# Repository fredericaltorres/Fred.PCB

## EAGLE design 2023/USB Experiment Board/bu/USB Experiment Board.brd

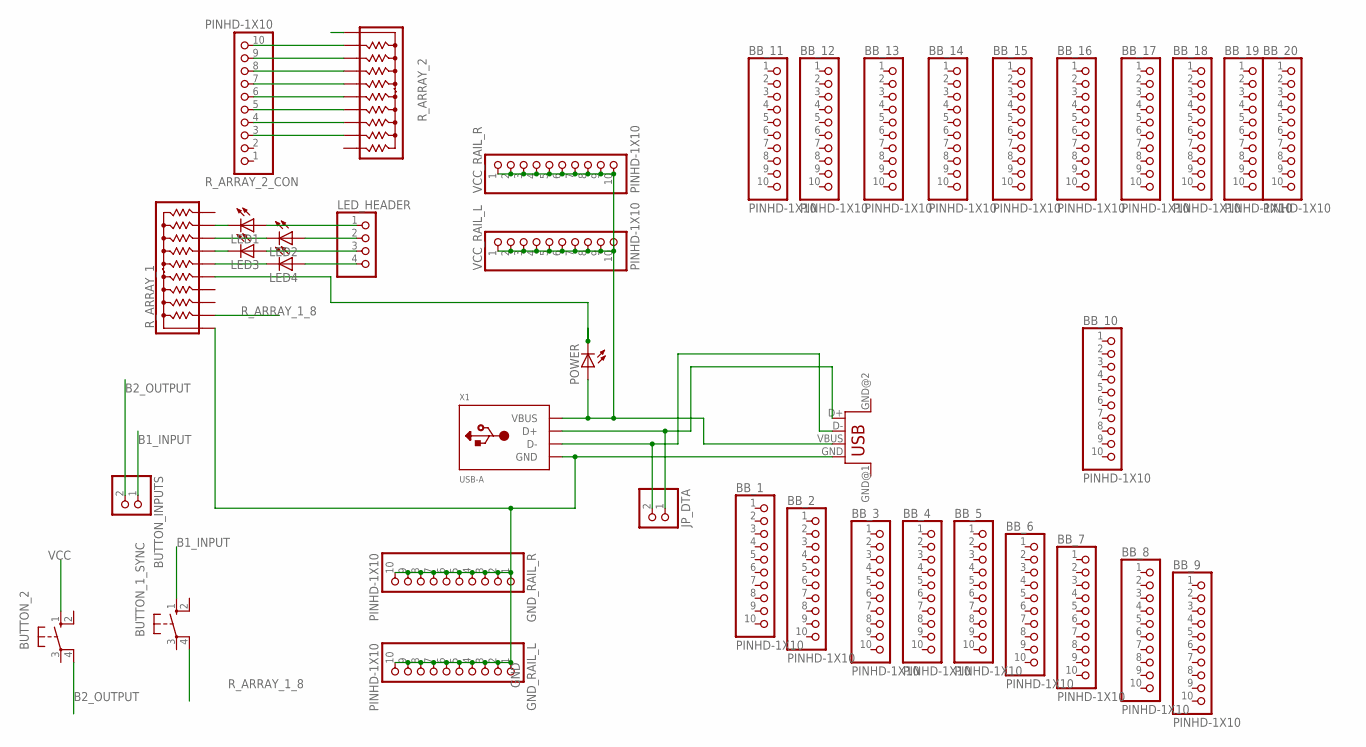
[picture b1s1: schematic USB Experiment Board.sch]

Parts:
BB_1, BB_2, BB_3, BB_4, BB_5, BB_6, BB_7, BB_8, BB_9, BB_10, BB_11, BB_12, BB_13, BB_14, BB_15, BB_16, BB_17, BB_18, BB_19, BB_20: PINHD-1X10; 1X10-BIG
BUTTON_1_SYNC, BUTTON_2: 10-XX; B3F-10XX
BUTTON_INPUTS: PINHD-1X2; 1X02
GND_RAIL_L: PINHD-1X10; 1X10-BIG
GND_RAIL_R: PINHD-1X10; 1X10-BIG
JP_DTA: PINHD-1X2; 1X02
LED1, LED2, LED3, LED4: LEDSMT1206; 1206
LED_HEADER: PINHD-1X4; 1X04
POWER: LEDSMT1206; 1206
R_ARRAY_1, R_ARRAY_2: 4610X; SIP10
R_ARRAY_2_CON: PINHD-1X10; 1X10-BIG
U$1: USB; USB-FEMALE-A-PTH
VCC_RAIL_L: PINHD-1X10; 1X10-BIG
VCC_RAIL_R: PINHD-1X10; 1X10-BIG
X1: USB-A; MOLEX_480371000

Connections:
B1_INPUT: BUTTON_1_SYNC.1 (S), BUTTON_INPUTS.1
B2_OUTPUT: BUTTON_2.4 (P1), BUTTON_INPUTS.2
GND: GND_RAIL_L.1, GND_RAIL_L.2, GND_RAIL_L.3, GND_RAIL_L.4, GND_RAIL_L.5, GND_RAIL_L.6, GND_RAIL_L.7, GND_RAIL_L.8, GND_RAIL_L.9, GND_RAIL_L.10, GND_RAIL_R.1, GND_RAIL_R.2, GND_RAIL_R.3, GND_RAIL_R.4, GND_RAIL_R.5, GND_RAIL_R.6, GND_RAIL_R.7, GND_RAIL_R.8, GND_RAIL_R.9, GND_RAIL_R.10, R_ARRAY_1.1, R_ARRAY_2.1, U$1.GND, X1.4 (GND)
unnamed: R_ARRAY_2.2, R_ARRAY_2_CON.10
unnamed: LED1.C, R_ARRAY_1.9
unnamed: JP_DTA.1, U$1.D+, X1.3 (D+)
unnamed: JP_DTA.2, U$1.D-, X1.2 (D-)
unnamed: LED2.C, R_ARRAY_1.8
unnamed: LED3.C, R_ARRAY_1.7
unnamed: LED4.C, R_ARRAY_1.6
unnamed: LED1.A, LED_HEADER.1
unnamed: LED2.A, LED_HEADER.2
unnamed: LED3.A, LED_HEADER.3
unnamed: LED4.A, LED_HEADER.4
unnamed: R_ARRAY_2.3, R_ARRAY_2_CON.9
unnamed: POWER.C, R_ARRAY_1.5
unnamed: R_ARRAY_2.4, R_ARRAY_2_CON.8
unnamed: R_ARRAY_2.5, R_ARRAY_2_CON.7
unnamed: R_ARRAY_2.6, R_ARRAY_2_CON.6
unnamed: R_ARRAY_2.7, R_ARRAY_2_CON.5
unnamed: R_ARRAY_2.8, R_ARRAY_2_CON.4
unnamed: R_ARRAY_2.9, R_ARRAY_2_CON.3
R_ARRAY_1_8: BUTTON_1_SYNC.4 (P1), R_ARRAY_1.2
VCC: BUTTON_2.1 (S), POWER.A, U$1.VBUS, VCC_RAIL_L.1, VCC_RAIL_L.2, VCC_RAIL_L.3, VCC_RAIL_L.4, VCC_RAIL_L.5, VCC_RAIL_L.6, VCC_RAIL_L.7, VCC_RAIL_L.8, VCC_RAIL_L.9, VCC_RAIL_L.10, VCC_RAIL_R.1, VCC_RAIL_R.2, VCC_RAIL_R.3, VCC_RAIL_R.4, VCC_RAIL_R.5, VCC_RAIL_R.6, VCC_RAIL_R.7, VCC_RAIL_R.8, VCC_RAIL_R.9, VCC_RAIL_R.10, X1.1 (VBUS)

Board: 2 copper layers, 39 parts (0 on the bottom side), 24 nets, no tracks yet.

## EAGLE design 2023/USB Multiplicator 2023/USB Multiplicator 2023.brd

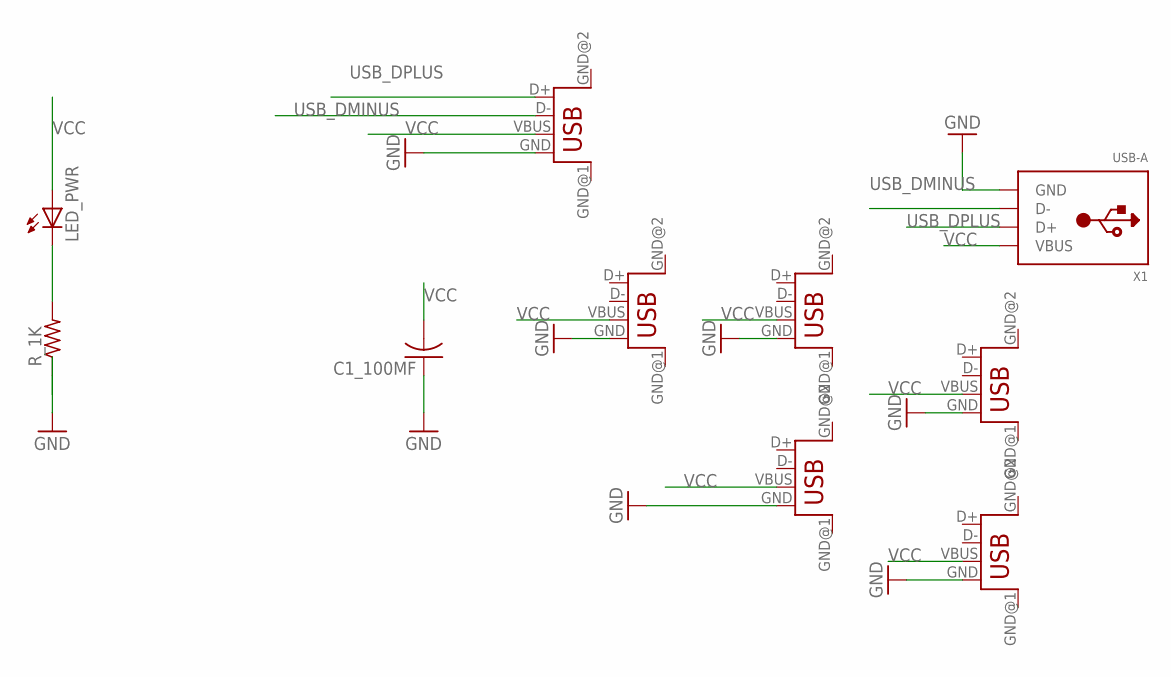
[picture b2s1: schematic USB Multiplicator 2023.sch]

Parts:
C1_100MF: C-US025-030X050; C025-030X050
LED_PWR: LEDSMT1206; 1206
R_1K: R-US_R1206; R1206
USB_OUT_2, USB_OUT_3, USB_OUT_4, USB_OUT_5, USB_OUT_6: USB; USB-FEMALE-A-PTH
USB_OUT_WITH_DATA_1: USB; USB-FEMALE-A-PTH
X1: USB-A; MOLEX_480371000

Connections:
GND: C1_100MF.1, R_1K.1, USB_OUT_2.GND, USB_OUT_3.GND, USB_OUT_4.GND, USB_OUT_5.GND, USB_OUT_6.GND, USB_OUT_WITH_DATA_1.GND, X1.4 (GND)
unnamed: LED_PWR.C, R_1K.2
USB_DMINUS: USB_OUT_WITH_DATA_1.D-, X1.2 (D-)
USB_DPLUS: USB_OUT_WITH_DATA_1.D+, X1.3 (D+)
VCC: C1_100MF.2, LED_PWR.A, USB_OUT_2.VBUS, USB_OUT_3.VBUS, USB_OUT_4.VBUS, USB_OUT_5.VBUS, USB_OUT_6.VBUS, USB_OUT_WITH_DATA_1.VBUS, X1.1 (VBUS)

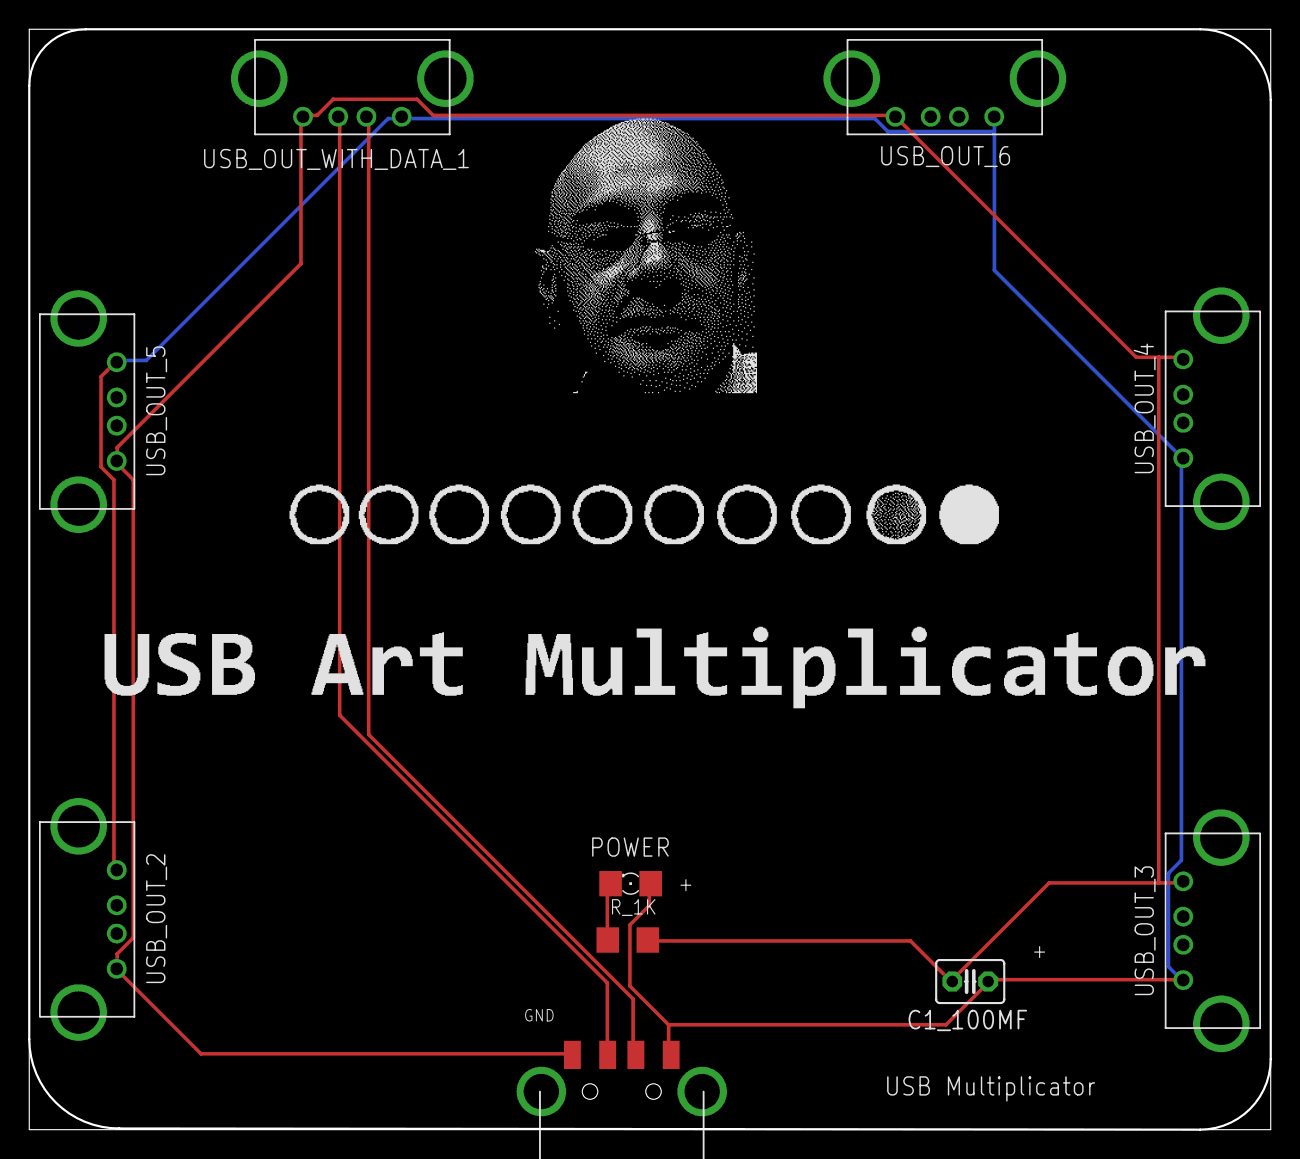
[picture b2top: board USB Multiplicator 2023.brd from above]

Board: 2 copper layers, 88.0 x 78.0 mm, 10 parts (0 on the bottom side), 5 nets.

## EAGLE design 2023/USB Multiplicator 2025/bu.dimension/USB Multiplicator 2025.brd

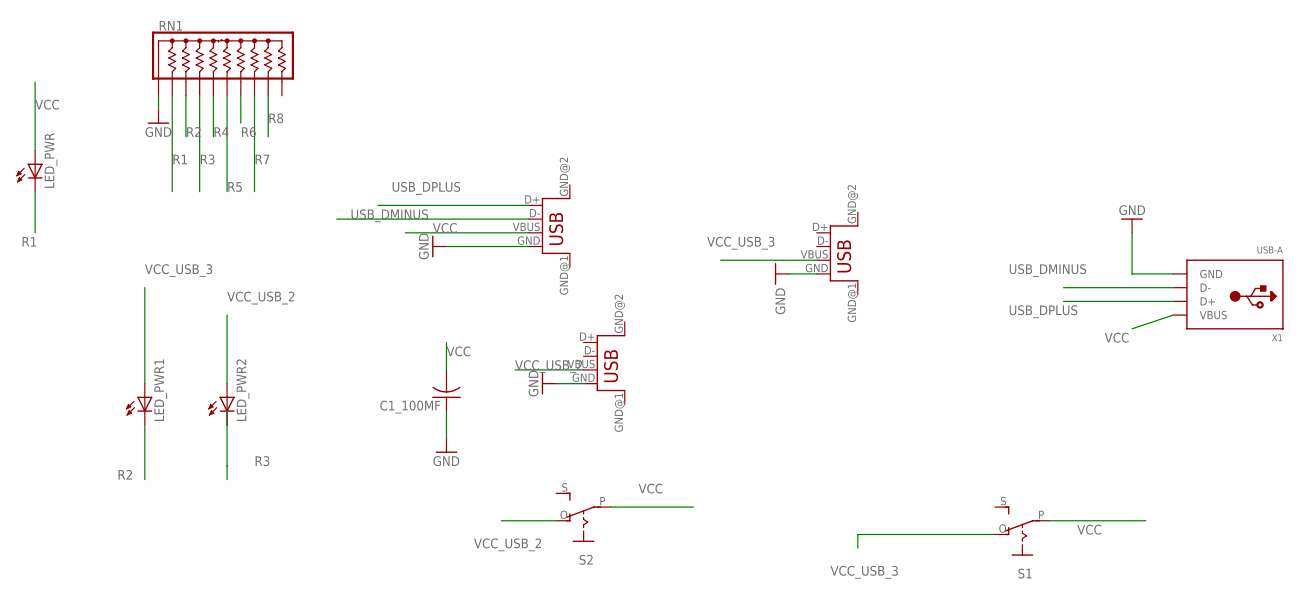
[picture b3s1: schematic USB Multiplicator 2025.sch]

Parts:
C1_100MF: C-US025-030X050; C025-030X050
LED_PWR, LED_PWR1, LED_PWR2: LEDSMT1206; 1206
RN1: 4610X; SIP10
S1, S2: EG1218S; EG1218
USB_OUT_1, USB_OUT_2: USB; USB-FEMALE-A-PTH
USB_OUT_WITH_DATA_1: USB; USB-FEMALE-A-PTH
X1: USB-A; MOLEX_480371000

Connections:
GND: C1_100MF.1, RN1.1, USB_OUT_1.GND, USB_OUT_2.GND, USB_OUT_WITH_DATA_1.GND, X1.4 (GND)
unnamed: USB_OUT_WITH_DATA_1.D-, X1.2 (D-)
unnamed: USB_OUT_WITH_DATA_1.D+, X1.3 (D+)
R1: LED_PWR.C, RN1.2
R2: LED_PWR1.C, RN1.3
R3: LED_PWR2.C, RN1.4
R4: RN1.5
R5: RN1.6
R6: RN1.7
R7: RN1.8
R8: RN1.9
VCC: C1_100MF.2, LED_PWR.A, S1.P, S2.P, USB_OUT_WITH_DATA_1.VBUS, X1.1 (VBUS)
VCC_USB_2: LED_PWR2.A, S2.O, USB_OUT_2.VBUS
VCC_USB_3: LED_PWR1.A, S1.O, USB_OUT_1.VBUS

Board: 2 copper layers, 11 parts (0 on the bottom side), 9 nets, no tracks yet.

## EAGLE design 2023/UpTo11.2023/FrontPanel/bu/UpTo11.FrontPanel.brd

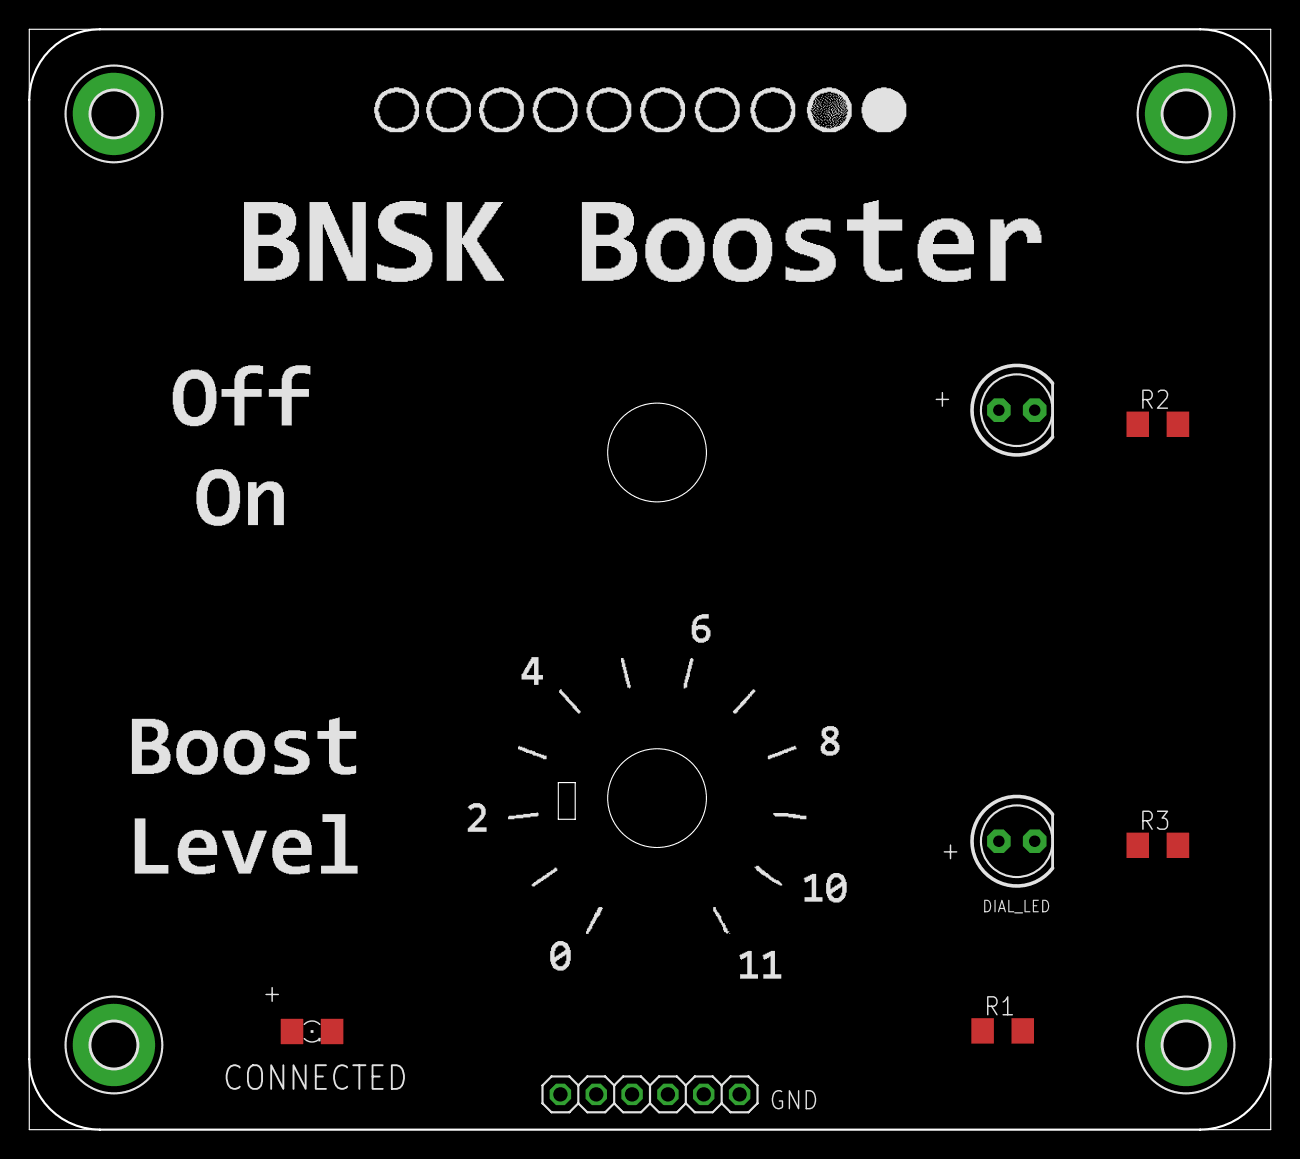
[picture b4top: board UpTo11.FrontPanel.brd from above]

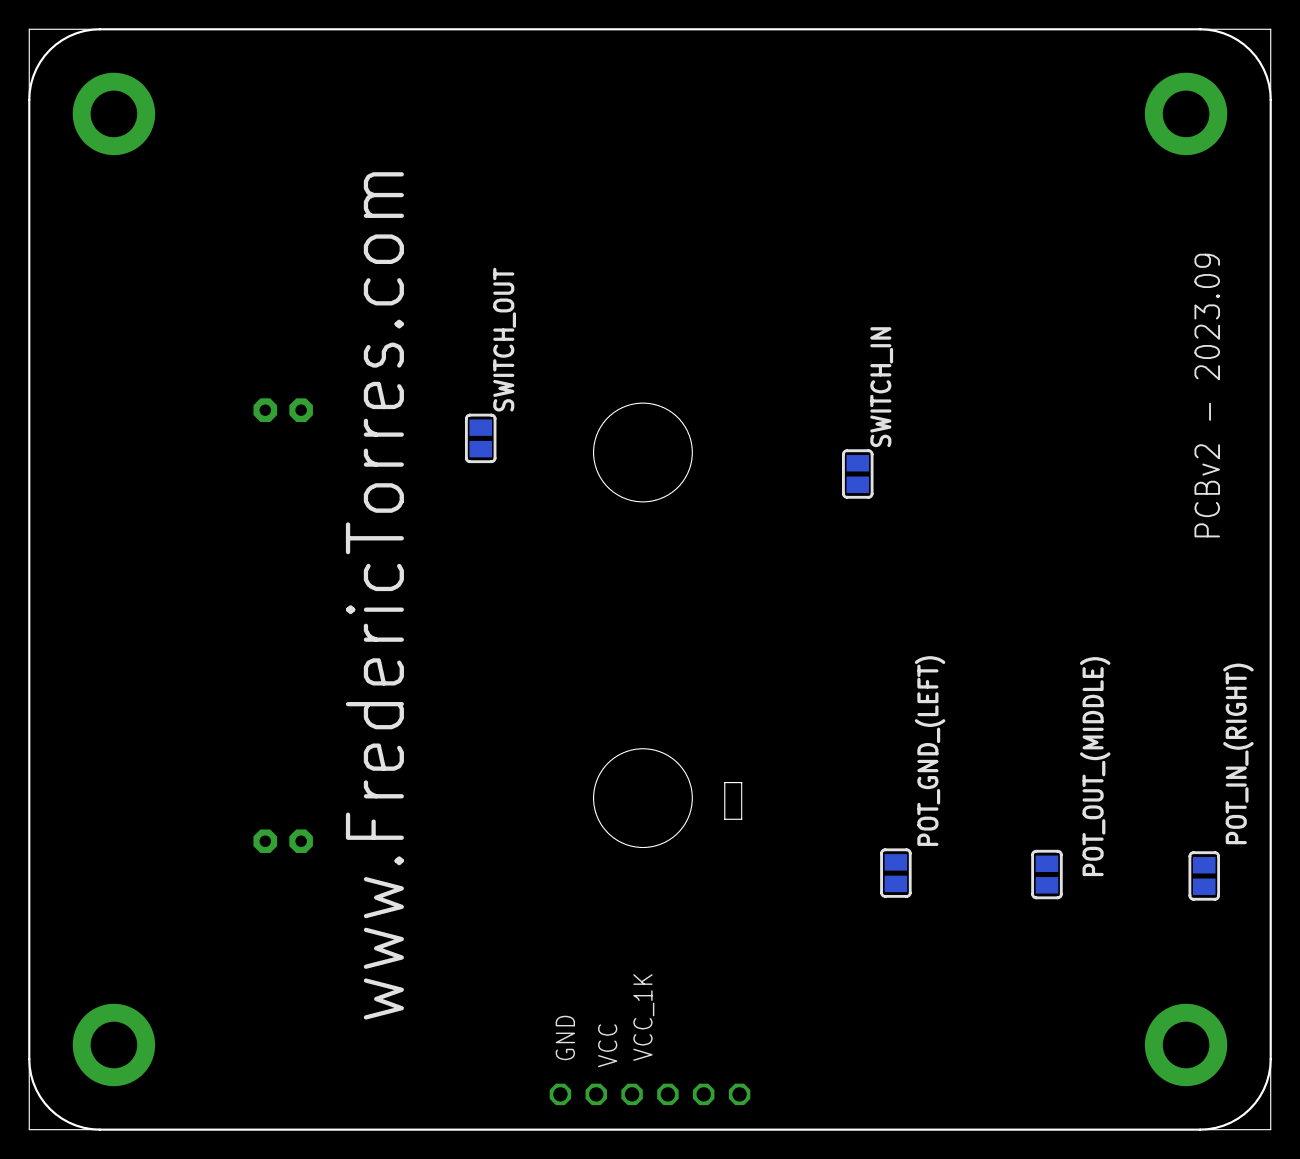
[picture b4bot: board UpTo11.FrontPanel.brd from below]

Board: 2 copper layers, 88.0 x 78.0 mm, 16 parts (5 on the bottom side), 7 nets, no tracks yet.

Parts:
BOOSTER_ON_LED: LED5MM
CONNECTED: 1206
DIAL_LED: LED5MM
FRONT_PANEL_INTERFACE: 1X06
H1, H2, H3, H4: MOUNT-PAD-ROUND3.3; 3,3-PAD
POT_GND_(LEFT): SOLDERJUMPER_REFLOW
POT_IN_(RIGHT): SOLDERJUMPER_REFLOW
POT_OUT_(MIDDLE): SOLDERJUMPER_REFLOW
R1, R2, R3: R1206
SWITCH_IN: SOLDERJUMPER_REFLOW
SWITCH_OUT: SOLDERJUMPER_REFLOW

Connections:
BOOSTER_ON: BOOSTER_ON_LED.A, POT_IN_(RIGHT).2, SWITCH_OUT.2
DIAL_INPUT: DIAL_LED.A, POT_OUT_(MIDDLE).2
GND_EX: FRONT_PANEL_INTERFACE.1, POT_GND_(LEFT).2, R1.1, R2.1, R3.1
unnamed: CONNECTED.C, R1.2
unnamed: BOOSTER_ON_LED.K, R2.2
unnamed: DIAL_LED.K, R3.2
VCC: CONNECTED.A, FRONT_PANEL_INTERFACE.6, SWITCH_IN.2

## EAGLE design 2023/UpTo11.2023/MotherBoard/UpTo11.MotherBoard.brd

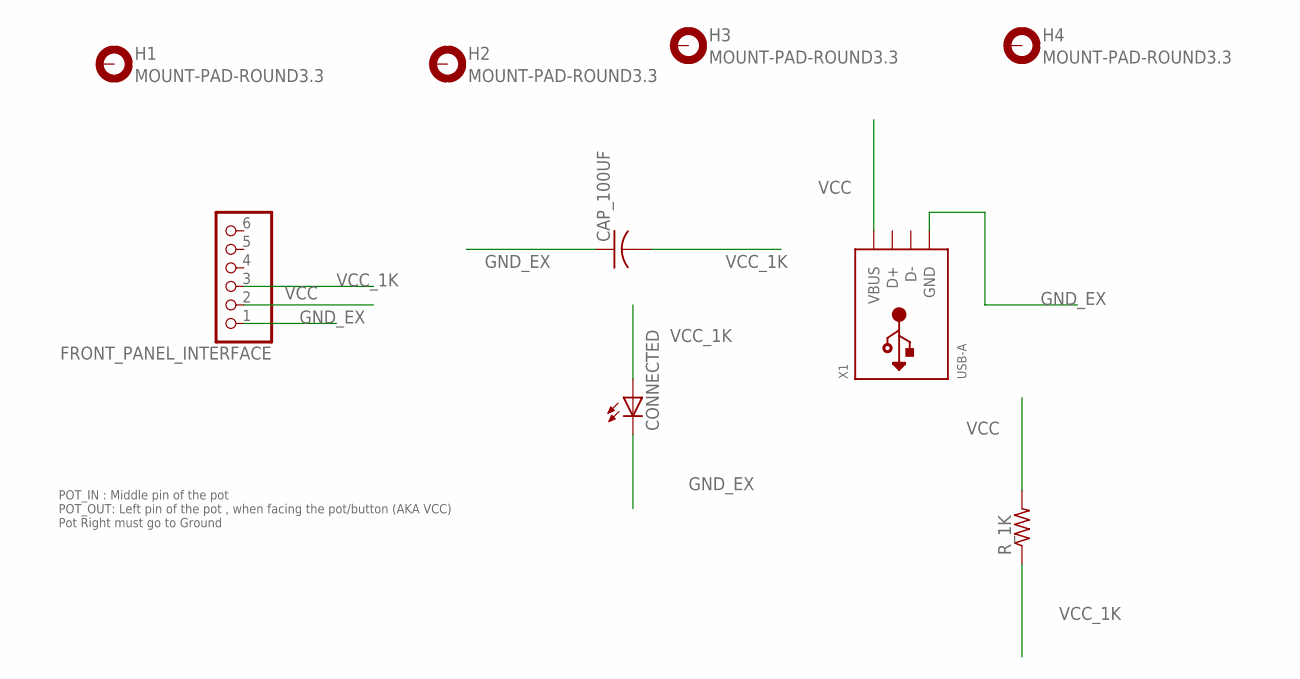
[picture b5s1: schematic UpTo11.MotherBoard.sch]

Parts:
CAP_100UF: C-US025-030X050; C025-030X050
CONNECTED: LEDSMT1206; 1206
FRONT_PANEL_INTERFACE: PINHD-1X6; 1X06
H1, H2, H3, H4: MOUNT-PAD-ROUND3.3; 3,3-PAD
R_1K: R-US_R1206; R1206
X1: USB-A; MOLEX_480371000

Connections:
GND_EX: CAP_100UF.1, CONNECTED.C, FRONT_PANEL_INTERFACE.1, X1.4 (GND)
VCC: FRONT_PANEL_INTERFACE.2, R_1K.2, X1.1 (VBUS)
VCC_1K: CAP_100UF.2, CONNECTED.A, FRONT_PANEL_INTERFACE.3, R_1K.1

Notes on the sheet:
POT_IN : Middle pin of the pot POT_OUT: Left pin of the pot , when facing the pot/button (AKA VCC) Pot Right must go to Ground

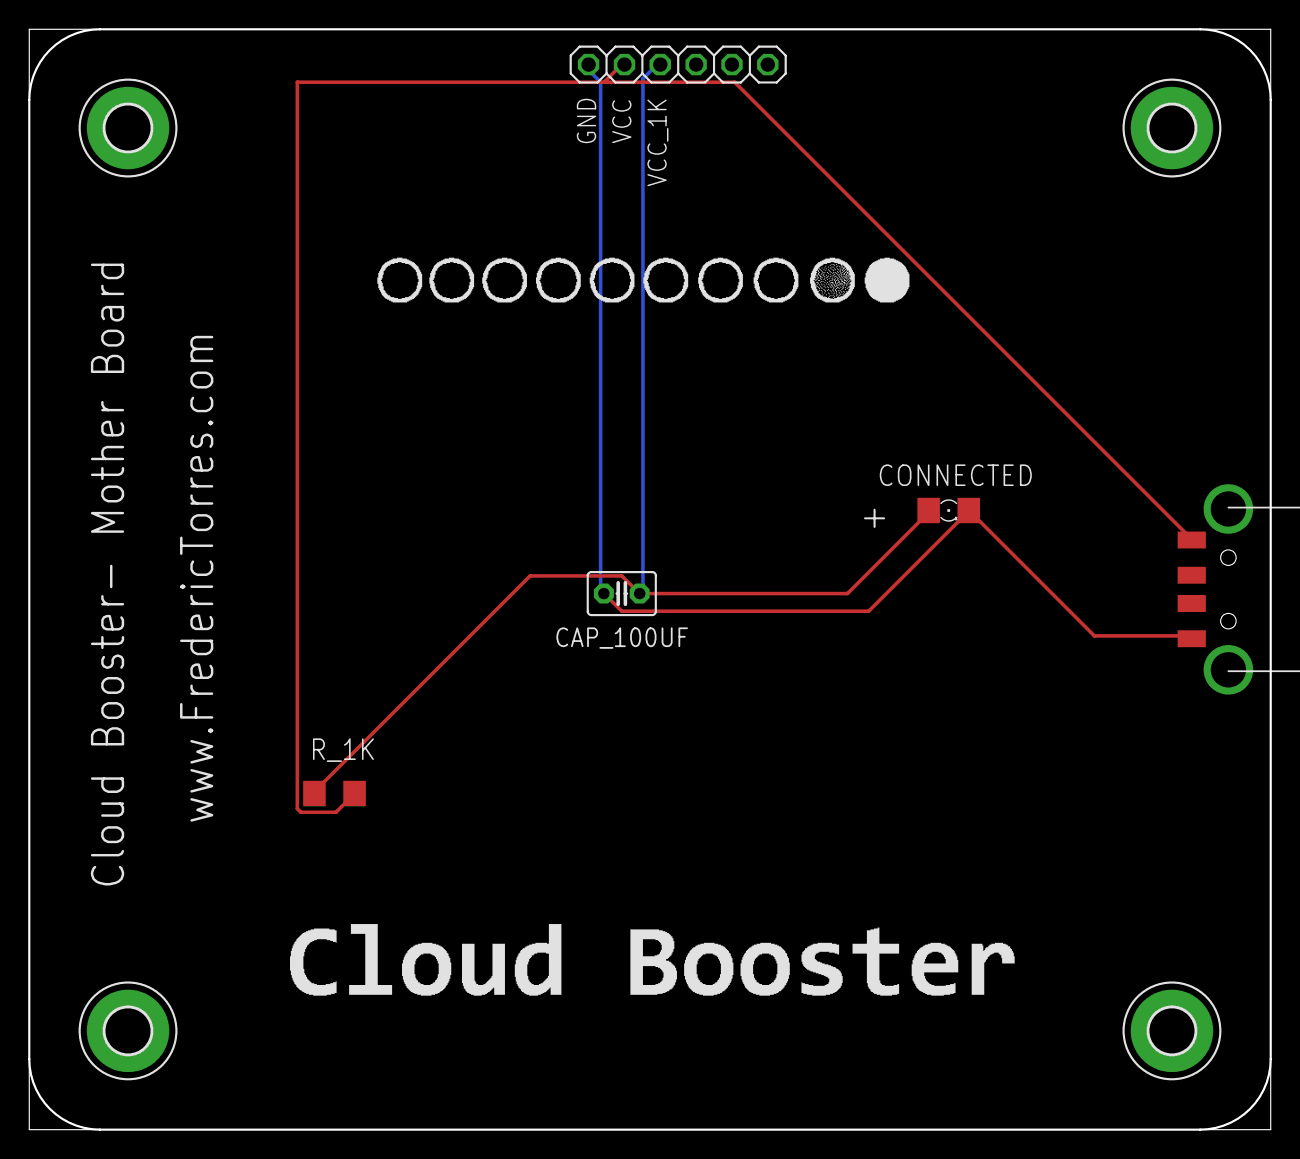
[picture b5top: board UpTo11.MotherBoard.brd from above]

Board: 2 copper layers, 88.0 x 78.0 mm, 9 parts (0 on the bottom side), 3 nets.

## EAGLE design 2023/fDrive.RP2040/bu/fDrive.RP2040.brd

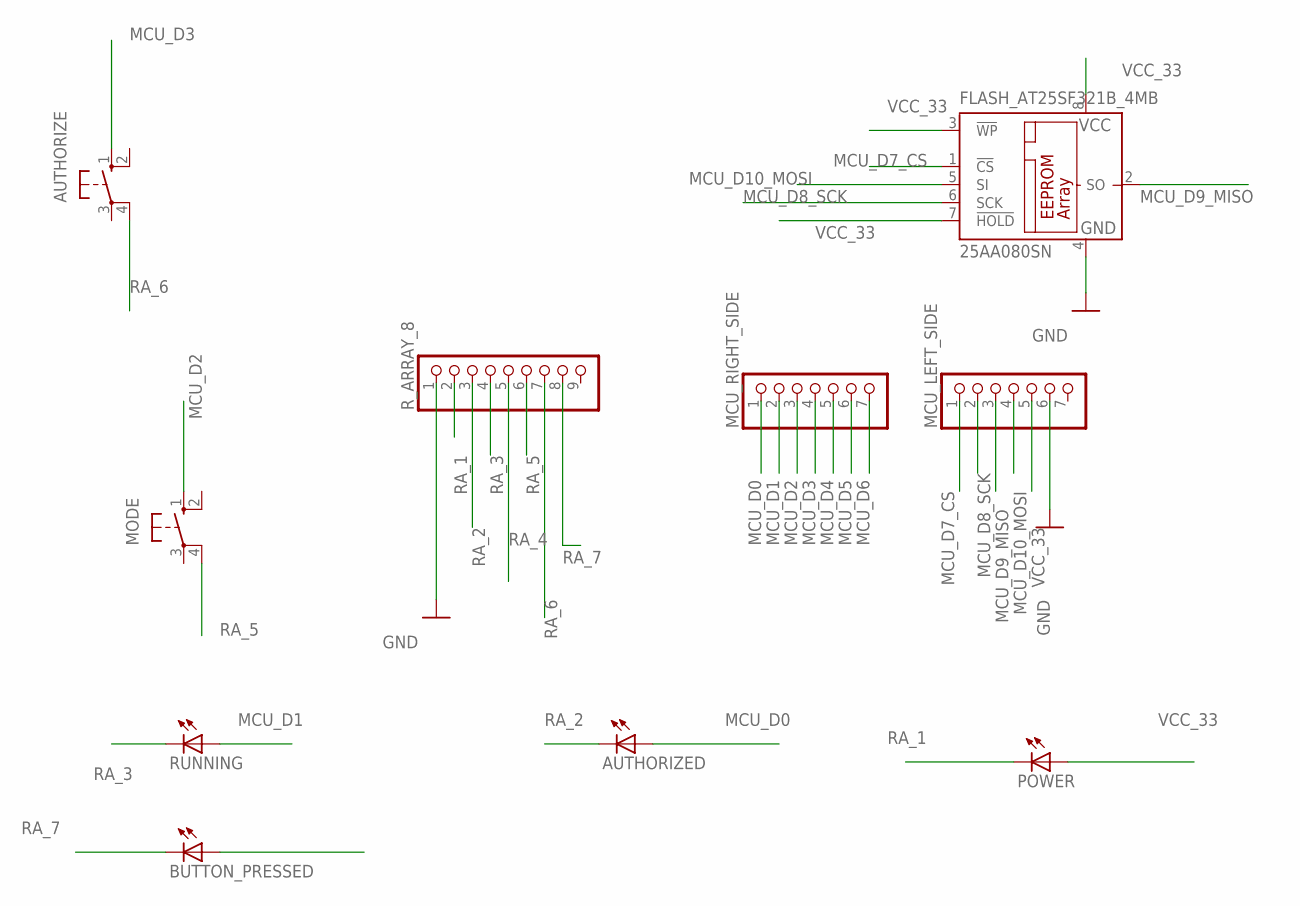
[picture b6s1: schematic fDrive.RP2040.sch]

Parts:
AUTHORIZE: 10-XX; B3F-10XX
AUTHORIZED: LEDSMT1206; 1206
BUTTON_PRESSED: LEDSMT1206; 1206
FLASH_AT25SF321B_4MB: 25AA080SN; SO-08
MCU_LEFT_SIDE: PINHD-1X7; 1X07
MCU_RIGHT_SIDE: PINHD-1X7; 1X07
MODE: 10-XX; B3F-10XX
POWER: LEDSMT1206; 1206
RUNNING: LEDSMT1206; 1206
R_ARRAY_8: PINHD-1X9; 1X09-BIG

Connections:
GND: FLASH_AT25SF321B_4MB.4 (GND), MCU_LEFT_SIDE.6, R_ARRAY_8.1
MCU_D0: AUTHORIZED.A, MCU_RIGHT_SIDE.1
MCU_D1: MCU_RIGHT_SIDE.2, RUNNING.A
MCU_D2: MCU_RIGHT_SIDE.3, MODE.1 (S)
MCU_D3: AUTHORIZE.1 (S), MCU_RIGHT_SIDE.4
MCU_D4: BUTTON_PRESSED.A, MCU_RIGHT_SIDE.5
MCU_D5: MCU_RIGHT_SIDE.6
MCU_D6: MCU_RIGHT_SIDE.7
MCU_D7_CS: FLASH_AT25SF321B_4MB.1 (!CS), MCU_LEFT_SIDE.1
MCU_D8_SCK: FLASH_AT25SF321B_4MB.6 (SCK), MCU_LEFT_SIDE.2
MCU_D9_MISO: FLASH_AT25SF321B_4MB.2 (SO), MCU_LEFT_SIDE.3
MCU_D10_MOSI: FLASH_AT25SF321B_4MB.5 (SI), MCU_LEFT_SIDE.4
RA_1: POWER.C, R_ARRAY_8.2
RA_2: AUTHORIZED.C, R_ARRAY_8.3
RA_3: RUNNING.C, R_ARRAY_8.4
RA_4: R_ARRAY_8.5
RA_5: MODE.4 (P1), R_ARRAY_8.6
RA_6: AUTHORIZE.4 (P1), R_ARRAY_8.7
RA_7: BUTTON_PRESSED.C, R_ARRAY_8.8
VCC_33: FLASH_AT25SF321B_4MB.3 (!WP), FLASH_AT25SF321B_4MB.7 (!HOLD), FLASH_AT25SF321B_4MB.8 (VCC), MCU_LEFT_SIDE.5, POWER.A

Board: 2 copper layers, 10 parts (0 on the bottom side), 17 nets, no tracks yet.

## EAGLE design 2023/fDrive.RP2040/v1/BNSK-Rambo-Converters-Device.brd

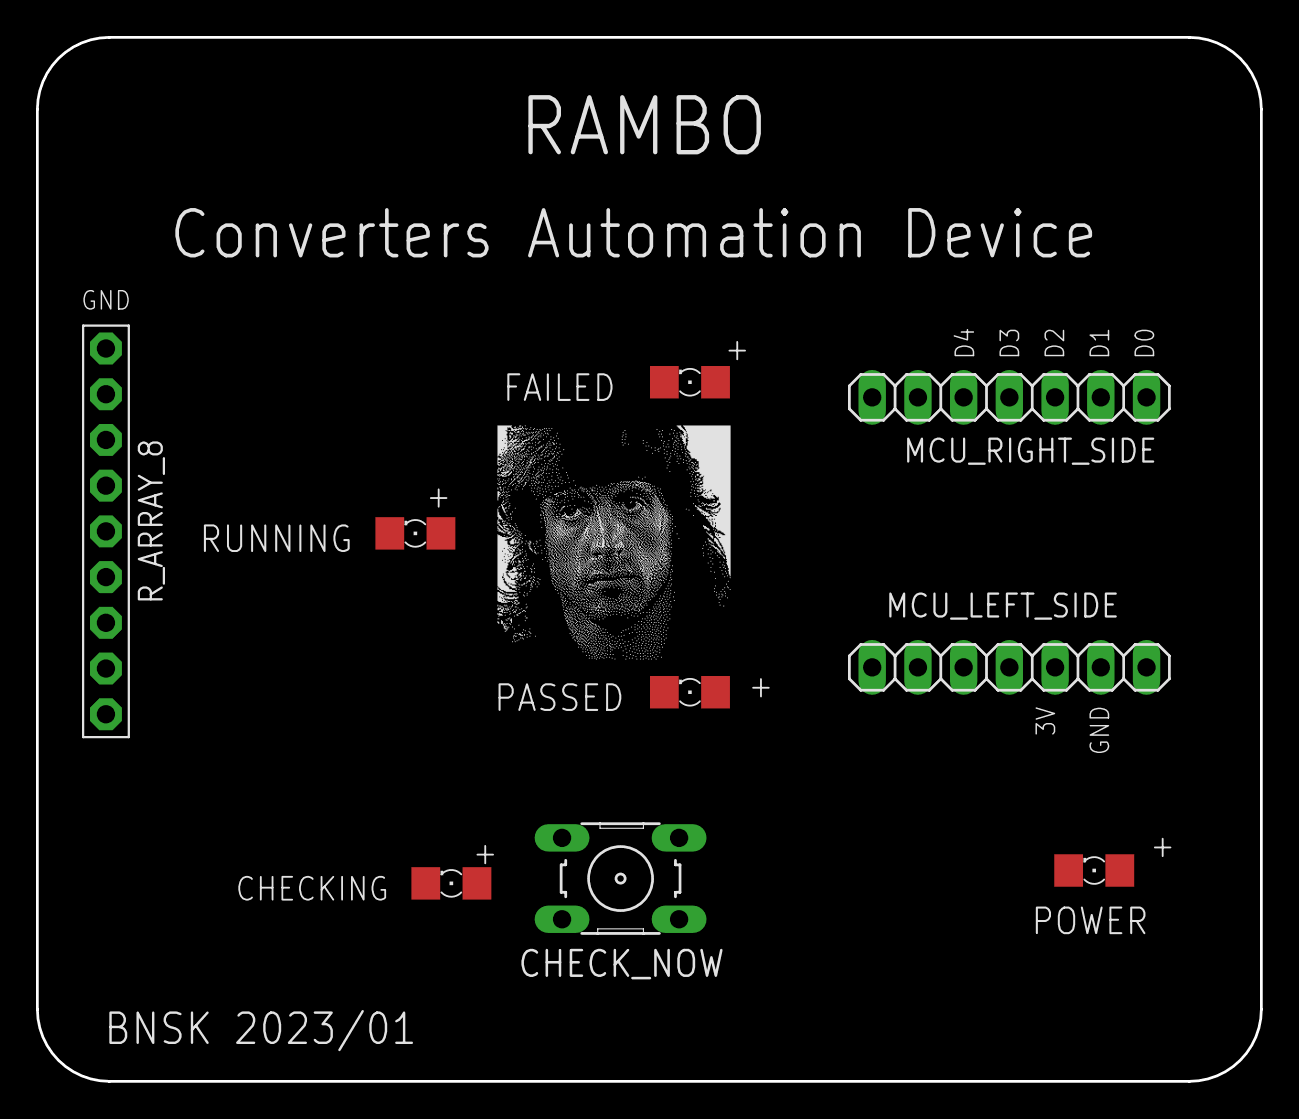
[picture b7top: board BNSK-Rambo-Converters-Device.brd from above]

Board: 2 copper layers, 68.0 x 58.0 mm, 9 parts (0 on the bottom side), 13 nets, no tracks yet.

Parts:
CHECKING: 1206
CHECK_NOW: B3F-10XX
FAILED: 1206
MCU_LEFT_SIDE: 1X07
MCU_RIGHT_SIDE: 1X07
PASSED: 1206
POWER: 1206
RUNNING: 1206
R_ARRAY_8: 1X09-BIG

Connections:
GND: MCU_LEFT_SIDE.6, R_ARRAY_8.1
MCU_D0: MCU_RIGHT_SIDE.1, PASSED.A
MCU_D1: FAILED.A, MCU_RIGHT_SIDE.2
MCU_D2: MCU_RIGHT_SIDE.3, RUNNING.A
MCU_D3: CHECK_NOW.1, MCU_RIGHT_SIDE.4
MCU_D4: CHECKING.A, MCU_RIGHT_SIDE.5
RA_1: POWER.C, R_ARRAY_8.2
RA_2: PASSED.C, R_ARRAY_8.3
RA_3: FAILED.C, R_ARRAY_8.4
RA_4: RUNNING.C, R_ARRAY_8.5
RA_5: CHECK_NOW.4, R_ARRAY_8.6
RA_6: CHECKING.C, R_ARRAY_8.7
VCC_33: MCU_LEFT_SIDE.5, POWER.A

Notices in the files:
parts and their libraries:
microbuilder: This work is placed in the public domain, and may be freely used for commercial and non-commercial work with the following conditions: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
